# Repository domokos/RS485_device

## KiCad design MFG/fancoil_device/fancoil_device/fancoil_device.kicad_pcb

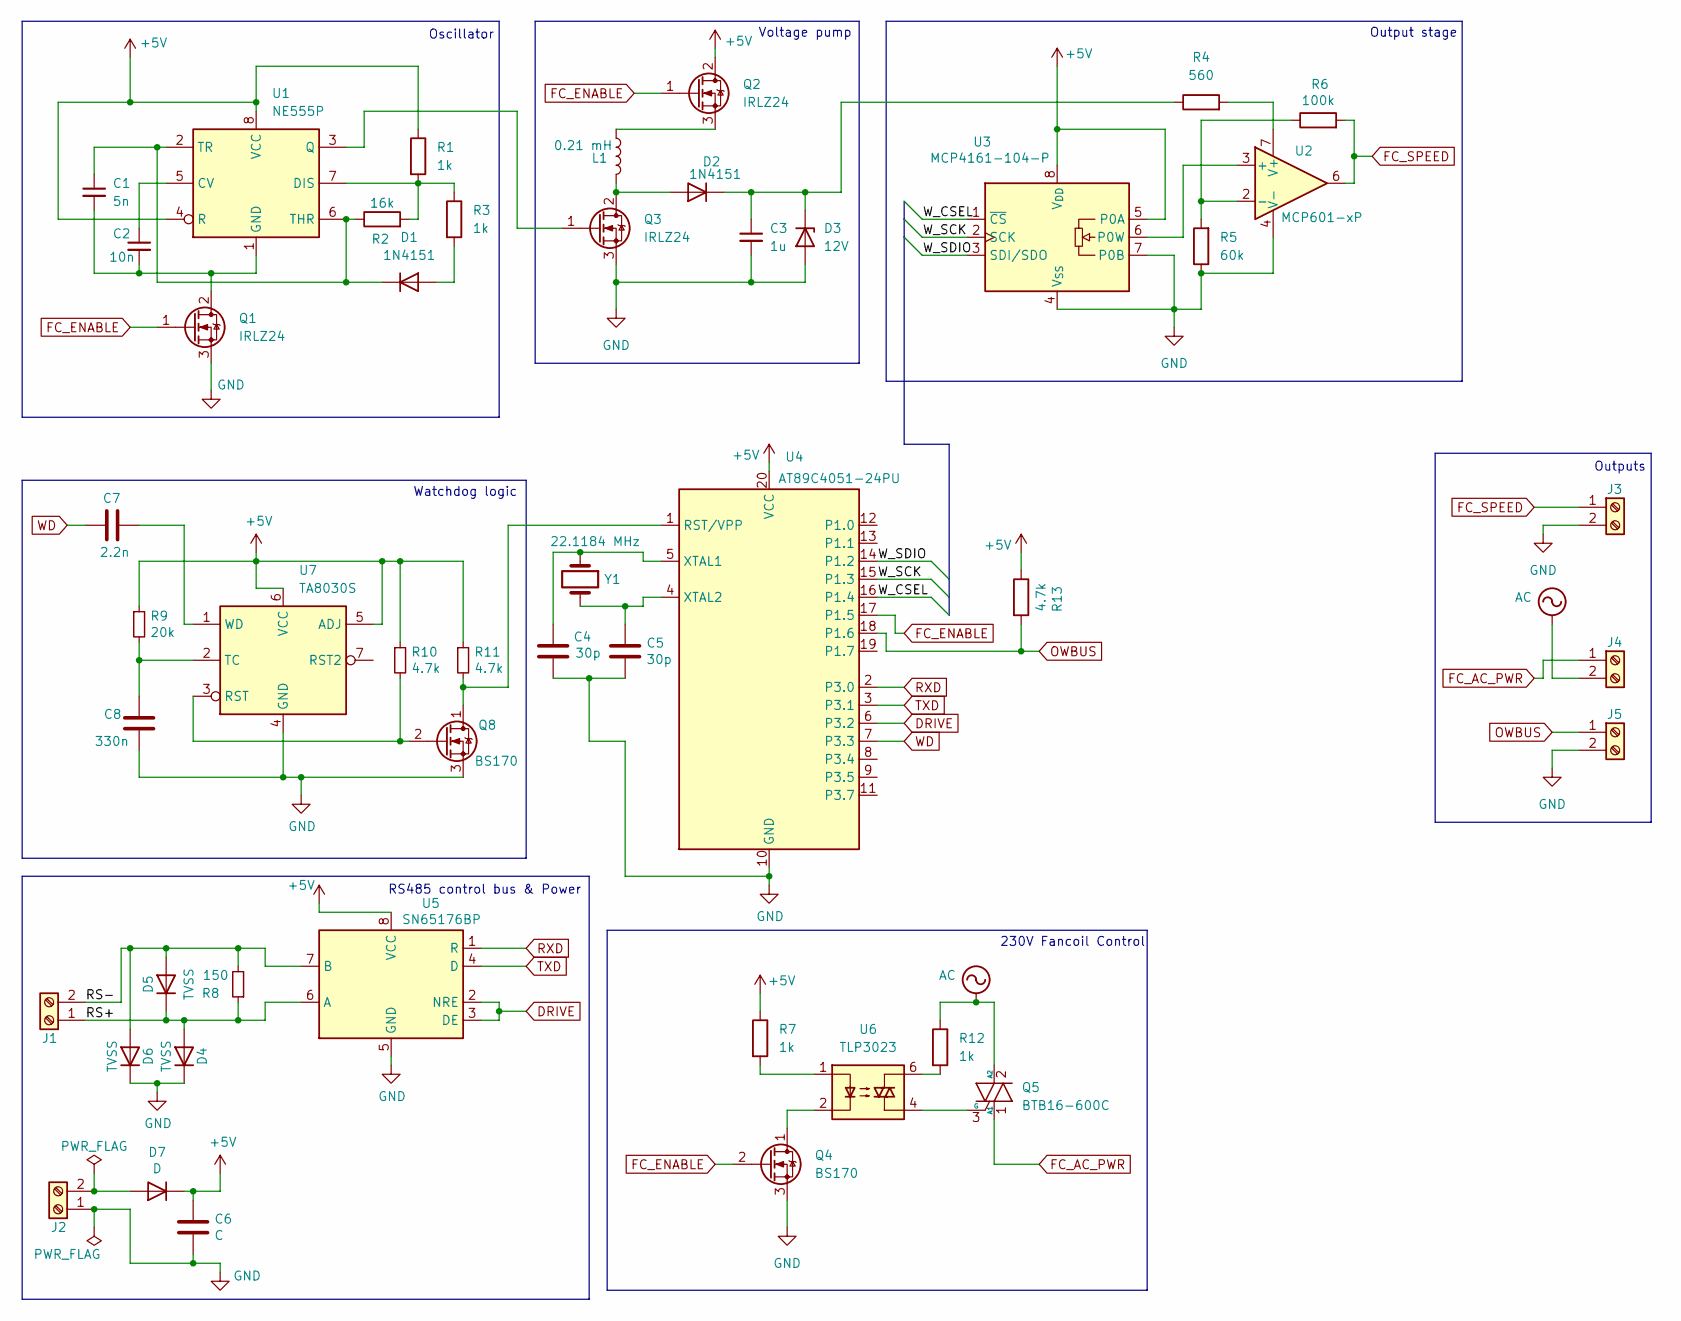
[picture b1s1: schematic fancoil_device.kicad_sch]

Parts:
C1: 5n; C_Disc_D9.0mm_W2.5mm_P5.00mm
C2: 10n; C_Disc_D3.0mm_W2.0mm_P2.50mm
C3: 1u; CP_Radial_Tantal_D4.5mm_P2.50mm
C4, C5: 30p; C_Disc_D3.8mm_W2.6mm_P2.50mm
C6: C; C_Radial_D6.3mm_H11.0mm_P2.50mm
C7: 2.2n; C_Disc_D3.8mm_W2.6mm_P2.50mm
C8: 330n; C_Disc_D3.8mm_W2.6mm_P2.50mm
D1, D2: 1N4151; D_DO-35_SOD27_P7.62mm_Horizontal
D3: 12V; D_A-405_P7.62mm_Horizontal
D4, D5, D6: TVSS; D_5W_P10.16mm_Horizontal
D7: D; D_A-405_P10.16mm_Horizontal
J1, J2, J3, J4, J5: Screw_Terminal_01x02; TerminalBlock_Phoenix_MKDS-1,5-2_1x02_P5.00mm_Horizontal
L1: 0.21 mH; L_Radial_D8.7mm_P5.00mm_Fastron_07HCP
Q1, Q2, Q3: IRLZ24; TO-220-3_Vertical
Q4, Q8: BS170; TO-92_Inline
Q5: BTB16-600C; TO-220-3_Vertical
R1, R3, R7, R12: 1k; R_Axial_DIN0204_L3.6mm_D1.6mm_P5.08mm_Horizontal
R2: 16k; R_Axial_DIN0204_L3.6mm_D1.6mm_P5.08mm_Horizontal
R4: 560; R_Axial_DIN0204_L3.6mm_D1.6mm_P5.08mm_Horizontal
R5: 60k; R_Axial_DIN0207_L6.3mm_D2.5mm_P10.16mm_Horizontal
R6: 100k; R_Axial_DIN0204_L3.6mm_D1.6mm_P5.08mm_Horizontal
R8: 150; R_Axial_DIN0204_L3.6mm_D1.6mm_P5.08mm_Horizontal
R9: 20k; R_Axial_DIN0204_L3.6mm_D1.6mm_P5.08mm_Horizontal
R10, R11, R13: 4.7k; R_Axial_DIN0204_L3.6mm_D1.6mm_P5.08mm_Horizontal
U1: NE555P; DIP-8_W7.62mm
U2: MCP601-xP; DIP-8_W7.62mm
U3: MCP4161-104-P; DIP-8_W7.62mm
U4: AT89C4051-24PU; DIP-20_W7.62mm
U5: SN65176BP; DIP-8_W7.62mm
U6: TLP3023; Toshiba_11-7A9
U7: TA8030S; R_Array_SIP7
Y1: 22.1184 MHz; Crystal_HC49-4H_Vertical

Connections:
+5V: C6.1, D7.1 (K), Q2.2 (D), R1.1, R7.1, R9.1, R10.1, R11.1, R13.1, U1.4 (R), U1.8 (VCC), U3.5 (P0A), U3.8 (V_{DD}), U4.20 (VCC), U5.8 (VCC), U7.5 (ADJ), U7.6 (VCC)
/RS+: D4.2 (A), D5.1 (K), J1.1, R8.1, U5.6 (A)
/RS-: D5.2 (A), D6.2 (A), J1.2, R8.2, U5.7 (B)
/W_CSEL: U3.1 (~CS), U4.16 (P1.4)
/W_SCK: U3.2 (SCK), U4.15 (P1.3)
/W_SDIO: U3.3 (SDI/SDO), U4.14 (P1.2)
AC: J4.2, Q5.2 (A2), R12.1
DRIVE: U4.6 (P3.2), U5.2 (NRE), U5.3 (DE)
FC_AC_PWR: J4.1, Q5.1 (A1)
FC_ENABLE: Q1.1 (G), Q2.1 (G), Q4.2 (G), U4.17 (P1.5)
FC_SPEED: J3.1, R6.2, U2.6
GND: C3.2, C4.2, C5.2, C6.2, C8.2, D3.2 (A), D4.1 (K), D6.1 (K), J2.1, J3.2, J5.2, Q1.3 (S), Q3.3 (S), Q4.3 (S), Q8.3 (S), R5.1, U2.4 (V-), U3.4 (V_{SS}), U3.7 (P0B), U4.10 (GND), U5.5 (GND), U7.4 (GND)
unnamed: D1.2 (A), R3.2
unnamed: C1.1, D1.1 (K), R2.1, U1.2 (TR), U1.6 (THR)
unnamed: D2.2 (A), L1.2, Q3.2 (D)
unnamed: C3.1, D2.1 (K), D3.1 (K), R4.1
unnamed: D7.2 (A), J2.2
unnamed: C1.2, C2.2, Q1.2 (D), U1.1 (GND)
unnamed: L1.1, Q2.3 (S)
unnamed: Q3.1 (G), U1.3 (Q)
unnamed: Q4.1 (D), U6.2
unnamed: Q5.3 (G), U6.4
unnamed: Q8.1 (D), R11.2, U4.1 (RST/VPP)
unnamed: Q8.2 (G), R10.2, U7.3 (RST)
unnamed: R7.2, U6.1
unnamed: R12.2, U6.6
unnamed: C2.1, U1.5 (CV)
unnamed: R1.2, R2.2, R3.1, U1.7 (DIS)
unnamed: U2.3 (+), U3.6 (P0W)
unnamed: R5.2, R6.1, U2.2 (-)
unnamed: R4.2, U2.7 (V+)
unnamed: C4.1, U4.5 (XTAL1), Y1.1
unnamed: C5.1, U4.4 (XTAL2), Y1.2
unnamed: C8.1, R9.2, U7.2 (TC)
unnamed: C7.2, U7.1 (WD)
OWBUS: J5.1, R13.2, U4.18 (P1.6)
RXD: U4.2 (P3.0), U5.1 (R)
TXD: U4.3 (P3.1), U5.4 (D)
WD: C7.1, U4.7 (P3.3)

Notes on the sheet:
Outputs
Oscillator
230V Fancoil Control
Watchdog logic
Output stage
Voltage pump
RS485 control bus & Power

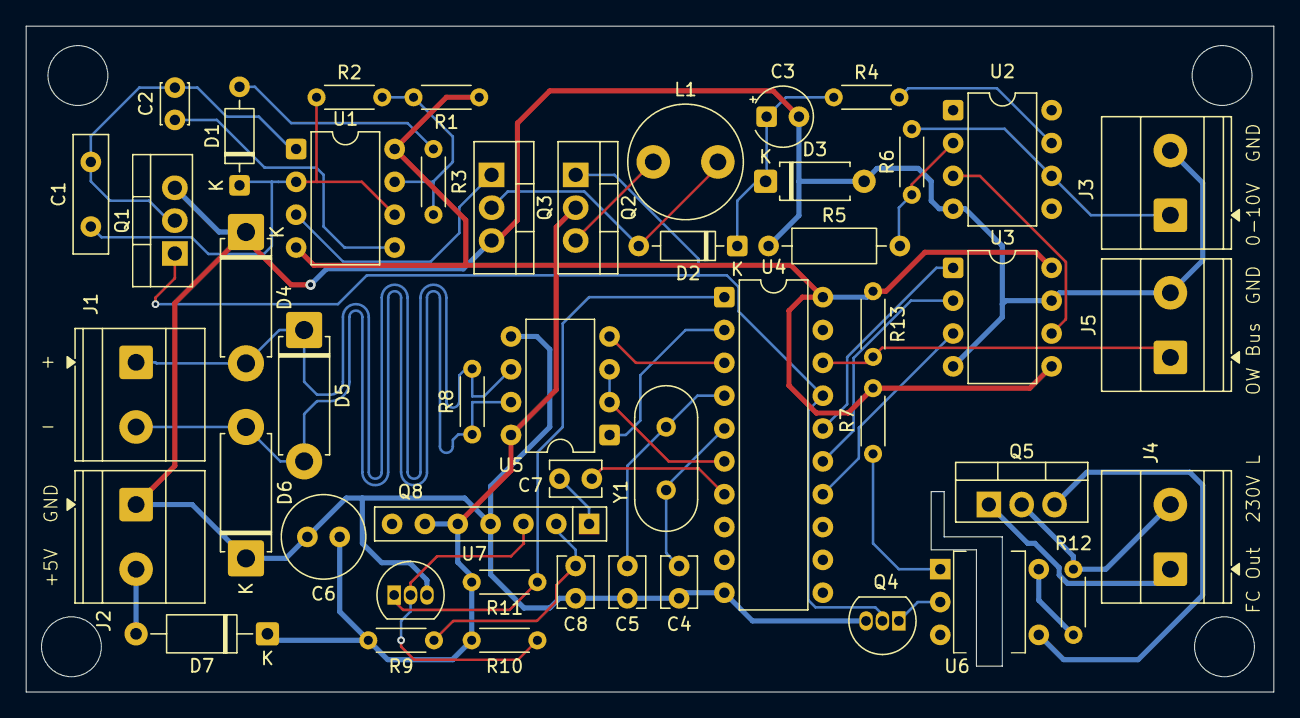
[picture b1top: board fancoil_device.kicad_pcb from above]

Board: 2 copper layers, 96.5 x 51.5 mm, 48 parts (0 on the bottom side), 39 nets.

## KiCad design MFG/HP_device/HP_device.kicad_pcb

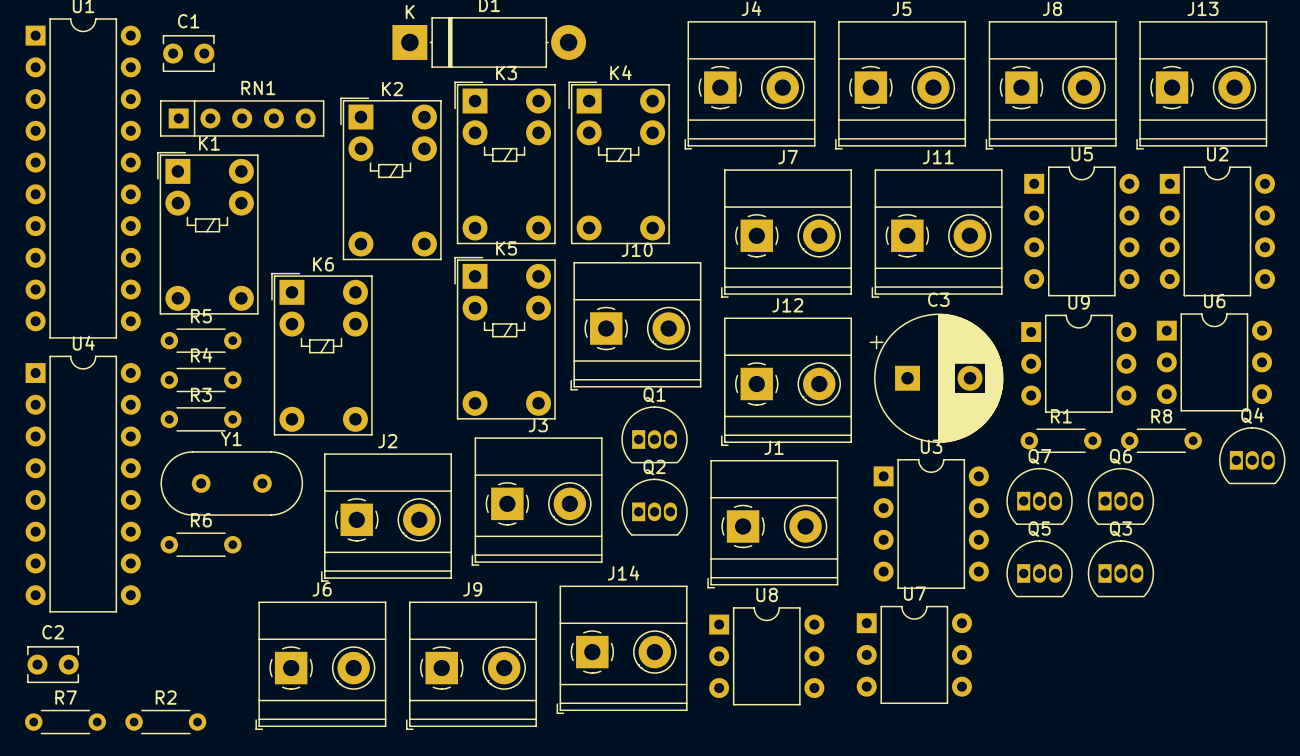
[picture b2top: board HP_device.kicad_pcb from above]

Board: 2 copper layers, 50 parts (0 on the bottom side), 64 nets, no tracks yet.

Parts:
C1, C2: C; C_Disc_D3.8mm_W2.6mm_P2.50mm
C3: C; CP_Radial_D10.0mm_P5.00mm
D1: D; D_5W_P12.70mm_Horizontal
J1, J2, J3, J4, J5, J6, J7, J8, J9, J10, J11, J12, J13, J14: Screw_Terminal_01x02; TerminalBlock_Phoenix_MKDS-1,5-2_1x02_P5.00mm_Horizontal
K1, K2, K3, K4, K5, K6: G5V-1; Relay_SPDT_Omron_G5V-1
Q1, Q2, Q3, Q4, Q5, Q6, Q7: BS170; TO-92_Inline
R1, R6, R7, R8: 4.7k; R_Axial_DIN0204_L3.6mm_D1.6mm_P5.08mm_Horizontal
R2: 200k; R_Axial_DIN0204_L3.6mm_D1.6mm_P5.08mm_Horizontal
R3, R4, R5: R_Small; R_Axial_DIN0204_L3.6mm_D1.6mm_P5.08mm_Horizontal
RN1: 4.7k; R_Array_SIP5
U1: AT89C4051-24PU; DIP-20_W7.62mm
U2: MCP4162-104; DIP-8_W7.62mm
U3: MCP4162-503; DIP-8_W7.62mm
U4: 74HC595; DIP-16_W7.62mm
U5: SN65176BP; DIP-8_W7.62mm
U6, U7, U8, U9: 4N25; DIP-6_W7.62mm
Y1: Crystal; Crystal_HC18-U_Vertical

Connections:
+5V: C3.1, D1.1, K1.2, K2.2, K3.2, K4.2, K5.2, K6.2, R1.1, R6.1, R7.1, R8.2, RN1.1, U1.20, U2.8, U3.8, U4.16, U5.8
/ALARM: RN1.5, U1.11, U9.5
/BCKUP: RN1.4, U1.9, U8.5
/C_DHW: K1.9, Q2.1
/C_DSET: K3.9, Q4.1
/C_LT: K6.9, Q7.1
/C_NOC: K5.9, Q6.1
/C_ON: K2.9, Q3.1
/C_OPM: K4.9, Q5.1
/DHW: Q2.2, U4.1
/DHWA: J9.1, K1.10
/DHWB: J9.2, K1.5, K1.6
/DSET: Q4.2, U4.3
/DSETA: J11.1, K3.10
/DSETB: J11.2, K3.5, K3.6
/EHS: RN1.2, U1.7, U6.5
/LT: Q7.2, U4.6
/LTA: J14.1, K6.10
/LTB: J14.2, K6.5, K6.6
/MODE: RN1.3, U1.8, U7.5
/NMR: U1.17, U4.10
/NOC: Q6.2, U4.5
/NOCA: J13.1, K5.10
/NOCB: J13.2, K5.5, K5.6
/NOE: U1.19, U4.13
/ON: Q3.2, U4.2
/ONA: J10.1, K2.10
/ONB: J10.2, K2.5, K2.6
/OPM: Q5.2, U4.4
/OPMA: J12.1, K4.10
/OPMB: J12.2, K4.5, K4.6
/SERDATA: R6.2, U1.12, U2.3, U3.3, U4.14
/SHCP: U1.16, U4.11
/STCP: U1.18, U4.12
/W_CSEL: Q1.2, R7.2, U1.13, U3.1
/W_SCK: U1.14, U2.2, U3.2
/W_SDO: U1.15, U2.7, U3.7
DRIVE: U1.6, U5.2, U5.3
GND: C1.2, C2.2, C3.2, J2.1, Q1.3, Q2.3, Q3.3, Q4.3, Q5.3, Q6.3, Q7.3, U1.10, U2.4, U3.4, U4.8, U5.5, U6.4, U7.4, U8.4, U9.4
unnamed: C1.1, U1.5, Y1.1
unnamed: C2.1, U1.4, Y1.2
unnamed: D1.2, J2.2
unnamed: J1.1, U5.6
unnamed: J1.2, U5.7
unnamed: J3.1, U6.2
unnamed: J3.2, R2.2
unnamed: J4.1, U7.2
unnamed: J4.2, R3.2
unnamed: J5.1, U8.2
unnamed: J5.2, R4.2
unnamed: J6.1, U9.2
unnamed: J6.2, R5.2
unnamed: J7.1, U2.5
unnamed: J7.2, U2.6
unnamed: J8.1, U3.5
unnamed: J8.2, U3.6
unnamed: Q1.1, R1.2, U2.1
unnamed: R2.1, U6.1
unnamed: R3.1, U7.1
unnamed: R4.1, U8.1
unnamed: R5.1, U9.1
unnamed: R8.1, U1.1
RXD: U1.2, U5.1
TXD: U1.3, U5.4

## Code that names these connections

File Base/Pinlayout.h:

/*
 * Pinlayout.h
 *
 *  Created on: Nov 25, 2014
 *      Author: dmolnar
 */

#ifndef PINLAYOUT_H_
#define PINLAYOUT_H_

/*
 *  This section defines the pins assignments of the microcontroller
 */
#ifdef __CDT_PARSER__

  #define MASTER_HOST_ID
  #define HOST_ID

  #define WATCHDOG_PIN
  #define COMM_DIRECTION_PIN
  // Define on which port the onewire interface is
  #define ONEWIRE_IS_ON_P1

#elif defined MASTER_CONTROLLER_DEVICE
  // Define the ID of this master
  #define MASTER_HOST_ID 1

  #define WATCHDOG_PIN P3_5
  #define COMM_DIRECTION_PIN P1_0

#elif defined MAIN_PANEL_SLAVE_DEVICE
  // The id of this host on the bus
  #define HOST_ID 11

  #define WATCHDOG_PIN P3_3
  #define COMM_DIRECTION_PIN P1_7
  // Define on which port the onewire interface is
  #define ONEWIRE_IS_ON_P3
  #define HEATER_RELAY_PIN P3_5 // Heater contact

#elif defined SIX_OWBUS_SLAVE_DEVICE
  // The id of this host on the bus
  #define HOST_ID 10

  #define WATCHDOG_PIN P3_5
  #define COMM_DIRECTION_PIN P3_7
  // Define on which port the onewire interface is
  #define ONEWIRE_IS_ON_P1

#elif defined MIXER_CONTROL_SLAVE_DEVICE
  // The id of this host on the bus
  #define HOST_ID 12

  #define WATCHDOG_PIN P3_3
  #define COMM_DIRECTION_PIN P1_7
  // Define on which port the onewire interface is
  #define ONEWIRE_IS_ON_P1

#elif defined HP_SLAVE_DEVICE
  // The id of this host on the bus
  #define HOST_ID 13

  #define COMM_DIRECTION_PIN P3_2
  #define EHS_PIN P3_7
  #define MODE_PIN P3_5
  #define BACKUP_PIN P3_4
  #define ALARM_PIN P3_3

#elif defined FANCOIL_SLAVE_DEVICE

  // The id of this host on the bus
  #define HOST_ID 14

  #define WATCHDOG_PIN P3_3
  #define COMM_DIRECTION_PIN P3_2
  // Define on which port the onewire interface is
  #define ONEWIRE_IS_ON_P1

#else
  #error "Basic pinlayout definitions could be determined"
#endif

#ifdef __CDT_PARSER__
  // Define the pins of the SPI interface of the MCP4161
  #define PIN_NCS_HW
  #define PIN_NCS_HEAT
  #define PIN_SCK
  #define PIN_SDI_SDO

  // Main panel heater pin
  #define HEATER_RELAY_PIN

  // Define the pins of the Extender interface of the MCP4161
  #define DS_PIN
  #define NOE_PIN
  #define STCP_PIN
  #define SHCP_PIN
  #define NMR_PIN

  // Define pins of the mixer controller
  #define CCW_PIN
  #define CW_PIN
  #define HW_HP_ONLY_PIN
  #define USEBUFFER_PIN
  #define GPIO_PIN

  // Define pins of the HP device
  #define EHS_PIN
  #define MODE_PIN
  #define BACKUP_PIN
  #define ALARM_PIN
  #define PIN_SERDATA
  #define PIN_SDO
  #define PIN_NCS_CSEL

  // Define pinns of the fancoil device
  #define PIN_FC_ACTIVE

#elif defined MAIN_PANEL_SLAVE_DEVICE
  // Define the pins of the SPI interface of the MCP4161
  #define PIN_NCS_HW P1_0
  #define PIN_NCS_HEAT P1_1
  #define PIN_SCK P3_7
  #define PIN_SDI_SDO P3_4

  // Heater contact
  #define HEATER_RELAY_PIN P3_5

  // Define the pins of the Extender interface
  #define DS_PIN P1_2
  #define NOE_PIN P1_3
  #define STCP_PIN P1_4
  #define SHCP_PIN P1_5
  #define NMR_PIN P1_6

#elif defined HP_SLAVE_DEVICE

  #define PIN_SERDATA P1_3

  // Define the pins of the SPI interface of the MCP4162
  #define PIN_NCS_CSEL P1_0
  #define PIN_SCK P1_1
  #define PIN_SDO P1_2

  // Define the pins of the Extender interface
  #define NOE_PIN P1_4
  #define STCP_PIN P1_5
  #define SHCP_PIN P1_6
  #define NMR_PIN P1_7

#elif defined SIX_OWBUS_SLAVE_DEVICE

#elif defined MASTER_CONTROLLER_DEVICE

#elif defined MIXER_CONTROL_SLAVE_DEVICE

  // Define pins of the mixer controller
  #define CCW_PIN P1_5
  #define CW_PIN P1_6
  #define HW_HP_ONLY_PIN P1_3
  #define USEBUFFER_PIN P1_4
  #define GPIO_PIN P3_7

#elif defined FANCOIL_SLAVE_DEVICE

  // Define the pins of the SPI interface of the MCP4161
  // In this case there is only one potentionmeter wiper in use so we define both chip selector pins to be the
  // same.
  #define PIN_NCS_HW P1_4
  #define PIN_NCS_HEAT P1_4
  #define PIN_SCK P1_3
  #define PIN_SDI_SDO P1_2
  #define PIN_FC_ACTIVE P1_5

#else
  #error "Device specific pinlayout definitions cannot be determined"
#endif

#endif /* PINLAYOUT_H_ */

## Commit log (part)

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2012-10-22 Sync laptop
2012-10-22 Adding functions.
2012-10-26 Fix memory options for build
2012-10-28 Slplit basic functions into a Base.c
2012-10-28 Rename serial to UART
2012-10-28 Add functions to Comm.c
2012-10-29 Start adding message processing logic
2012-10-29 Removing eclipse settings from the project.
2012-10-29 Fix ignoring build componenst on desktop.
2012-10-29 Fix encoding to ISO-8859-2.
2012-10-30 Finalize message reception logic
2012-10-30 Complete communication routines.
2012-10-30 Correct typo of buffer clearing.
2012-10-31 Get rid of the top level subdirectory structure.
2012-10-31 Fix: Put ISR prototypes in the same file that contains main().
2012-11-01 Fix interrupt enable and send buffer numbering.
2012-11-01 Fix messaging logic sync based on emulator tests.
2012-11-01 Add simple test. This commit works in the emulator.
2012-11-02 CRC16 working. / cleanup to use it.
2012-11-04 Implement flip_bit - not yet tested
2012-11-06 Bring bit flipping into the crc calculation. Not yet tested in emulator.
2012-11-06 Clean up Comm.h
2012-11-06 16 bit CSR calculation works with flippped bits in ermulator.
2012-11-10 CRC calculation works and tested in the emulator. TODO: Test response CRC
2012-11-10 CRC tested in-out in emulator. TODO:write tests for HW bus comm and test it :)
2013-01-29 Create own header file for at89c4051 registers to handle eclipse errors.
2013-02-01 Add interface functions to comm module
2013-02-01 Define message opcodes
2013-02-02 Reorganize functions
2013-02-04 Implement tests for hardware test.
2013-02-07 Fix documetation typos and cleanup prev_recieved char in Comm.c
2013-02-10 Add communication transciever handling
2013-02-11 Add flood test to the comm module.
2013-02-11 Fix some typo in comments and in CRC_ERROR #define
2013-02-11 Verify delay routines
2013-02-11 Moving to laptop
2013-02-12 Cleanup timeout calculation in receive message.
2013-02-12 SOme optimizations around receive state machine
2013-02-12 Fix test sequences
2013-02-13 Add testing facilities.
2013-02-15 Modifying test code
2013-02-16 Cleanup and implement circular buffer based UART communication
2013-02-16 Communication mode changed to length based and tested succesfully in the emulator.
2013-02-18 Reorganize into devices and master controller step1
2013-02-18 Reorganization almost done
2013-02-18 Finallize reorganization. Succesfully tested in emulator.
2013-02-19 Reorganize to implement Master controller.
2013-02-19 Reorganize: move common functionality into Comm_common module.
2013-02-19 Add master address and start implementing master conrtoller.
2013-02-19 Fix compile issues.
2013-02-19 Start implementing timer1 clock based messaging timeout counter for reliability and for bus master messaging timeout measurements.
2013-02-19 Change HI-LO timeout information to bit
2013-02-20 Add timeout handling routines
2013-02-20 Update calculations
2013-02-21 Reorganized delay and timeout to correct time base and test it in emulator.
2013-02-22 Bus master done todo: test it in emulator
2013-02-23 Workaround SDCC bug. Tested on protoboard. Works.
2013-02-24 COmments cleanup.
2013-02-24 Handle MSG_TOO_LONG in receiving
2013-02-25 Resove referencing NULL pointer as message buffer.
2013-02-26 Reorganize master communication and add new message types.
2013-02-27 Reorganize return values of get_messge
2013-02-27 Add onewire lib
2013-02-27 Continued onewire integration.
2013-02-28 MOdify onewire to accept pinmask and start onewire test implementation.
2013-02-28 Onewire tested in emulator
2013-03-01 Start temp measuring device and reorganize comm_speed based on two crystal speeds.
2013-03-01 Reorganized for generic device.
2013-03-01 Start ow temp measuring implementation
2013-03-01 Temp measure and read tone. Test it in emulator then with HW.
2013-03-02 Start temp reader device testing in emulator.
2013-03-02 1wire Measured with scope. Seems OK.
2013-03-03 Communicates temperature correctly on protoboard.
2013-03-04 add temp measurement timeout
2013-03-04 Investigating timeout. Not yet found.
    Device sometimes does not respond to messages getting to UART pin for
    unknown reason.
2013-03-05 Testing comm problems
2013-03-05 Clean testing code from master.
2013-03-05 Cleanup before branch
2013-03-05 Tested with scope & protoboard. Works.
2013-03-06 COmm error rate down to 4%. Hmmmm.
2013-03-06 Still errors a bit.
2013-03-06 Refine get_message
2013-03-06 Fixed timeout errors. Timeout error rate below 0.1%
2013-03-06 Distribute onewire reads in time.
2013-03-11 Add watchdog functionality.
2013-03-12 Refine timer in Base and equalize interrupt priorities
2013-03-12 Change watchdog pin.
2013-03-12 Add schematics
2013-03-12 Add symbols
2013-03-13 Start drawing schematic.
2013-03-14 Finish schematic.
2013-03-15 Add symbols, finalize schematic.
2013-03-15 Schematics refining
2013-03-15 Finalize resistor values.
2013-03-16 Change crystal frequency and make init timer pulic.
2013-03-16 Reorganize schematics and pcbs
2013-03-17 Work on pcb
2013-03-17 Refine serial tx.
2013-03-17 fix packaging of optocoupler.
2013-03-18 Refine pcb once more.
2013-03-18 Cleanup generated files.
2013-03-18 Add onewire 3 device
2013-03-18 Reorganize symbols.
2013-03-20 Rename things
2013-03-21 Finalize elements in ow6 layout
2013-03-21 Finish PCB
2013-03-21 fixups on layout.
2013-03-22 Prited PCBs.
2013-03-23 Add alignment marks to PCB layout
2013-03-25 Test the panel. MOdify watchdog resistor and ADJ values.
2013-03-29 Finalize master controller
2013-03-30 Add structure for main panel device based on generid test device.
2013-03-30 Reorganize further.
2013-03-31 Add registers.
2013-03-31 Write registers
2013-03-31 Master panel ready for HW testing.
2013-04-01 PWM is complete. Need to add PWM mesage handling before testing.
2013-04-02 Clarify comments.
2013-04-02 Implemented multiple OW devices on a single bus. Needs testing.
2013-04-02 PWM and single OW tested in hardware. Works. To be tested mutiple OW on a bus.
2013-04-03 Reorganize PWM
2013-04-03 OPtimize PWM state machine.
2013-04-03 Tested in device. Works.
2013-04-08 ROM ID read succesfully with test device.
2013-04-09 Multiple OW devices on single bus works, tested in Main Panel Device.
2013-04-11 Reorganize panels and add comm safety to Master controller.
2013-04-11 fix small typo.
2013-04-13 Prepare branching comm for interrupt driven serial receiving.
2013-04-13 Fix eclipse parser mocking.
2013-04-13 Messaging restructured. Ready for testing.
2013-04-16 REN based strategy in ISR receiving. Needs testing.
2013-04-16 Some ISR-receiver hadshaking and timeout fixes before testing.
2013-08-04 Modify layout of 6owbus - join powe & GND lines to a single connector.
2013-08-23 Add 6 ow bus device.
2013-08-25 OW interface of 6 OW bus device tested.
2013-08-28 Add alternative Master controller PCB
2013-08-31 Modify master controller layout
2013-08-31 Fine tune master controller pcb
2013-09-01 Finalize Master controller PCB layout
2013-09-03 Fine tune layout and add printed ps file
2013-09-16 Fix optocoupler in master_controller MFG
2013-10-01 New version of master_controller MFG
2013-12-28 Continue Design of main panel device
2014-01-19 Main controller PCB design started
2014-01-19 Further elaborate main controller MFG.
2014-01-23 Fix missing resistor and add 230V signal components
2014-01-25 Create 230V parts of board
2014-01-26 Finish first version of PCB fine tune layout connections.
2014-02-08 Fix wirting of optocoupler inputs.
2014-03-03 Change 230V capacitor to a bigger one.
2014-03-16 Add a different size line capacitor.
2014-03-17 Fine tune layout
2014-05-02 Add text and alignment mark to main panel PCB
2014-11-13 Modify main panel device for new condensing boiler.
2014-11-17 Revert a file
2014-11-18 Finalize board before printing
2014-11-23 Finalize layout. Correct Triac pinout and schematic.
2014-11-23 Fix relay pcb in main panel board
2014-11-23 Add MCP4161 code
2014-11-25 Reorganize pinlayout definitions.
2014-11-25 Fixed missing component from main panel device
2014-11-26 Fixes of the main panel device after first debugging session.
2014-11-26 Fix wiper setting.
2014-11-27 Fix spi timing for MCP4161
2014-11-27 Finalize and test rheostat timing
2014-11-30 Onewire device addresses set for final operation.
2014-11-30 Update contact comments in the controller code
2014-12-01 Fix HW problems and test.
2014-12-01 Fix typo in scaling
2014-12-07 Fix command bytes
2014-12-07 Re-fix wiper write volatility
2014-12-07 Fix reading wiper volatility flag
2014-12-14 Branch for time-distributed sensor read on the single bus
2014-12-15 Rework main panel schematic
2014-12-16 Finalize schematics - add 2 new switches and a rheostat
2014-12-16 Add original rheostat drawing
2014-12-17 Start working on pcb layout
2014-12-18 Develop layout further
    Please enter the commit message for your changes. Lines starting
2014-12-18 Finish Layout
2014-12-18 Reduce vias in the pcb
2014-12-19 Remove some vias
2014-12-24 Add mounting holes to pcb
2014-12-25 Reorganize board to make moore room
2014-12-25 Finalize layout
2014-12-26 Create hidraulic schematic
2014-12-26 Add alignment marks to the pcb layout
2014-12-26 Rename file
2014-12-27 Modify hidraulic drawing
2014-12-29 MOve main panel device to single extender code
2014-12-29 Fix extender reset and buffer initialize bugs.
2014-12-29 Swap extender bit order
2014-12-29 Adjust main panel device inactivity self-reset timeout to 30 sec
2014-12-29 Tested in Hardware - cleanup comments and contact assignments in code
2014-12-31 Disable messaging timeout as it did not work.
2014-12-31 Fix pinlayout defines by introducing device specfic compiler defines
2014-12-31 Make all pind device type define dependent
2015-01-01 Fix defines for Exclipes CDT parser
2015-01-03 Fix typo of Exclipse parser name
2015-01-03 Start implementing the owbus bridge
2015-01-03 Start HW testing six owbus device
2015-01-03 Prepare for in-HW testing
2015-01-03 Fix messaging
2015-01-03 Fix direction pin
2015-01-03 Swap search byte order
2015-01-03 Test owbuf in match active
2015-01-03 Fix typos in debug code
2015-01-03 Lab test preparation
2015-01-03 Restore real device addresses
2015-01-04 Fix ow temp measurement initiation
2015-01-04 Fix addressing of registers
2015-01-30 Create new device - compiles
2015-02-03 Add layout elements for mixer controller
2015-02-04 Finish schematic - create initial PCB
2015-02-06 Finalize layout of mixer controller
2015-02-11 Prepare mixer logic
2015-02-14 Finalize mixer controller
2015-02-14 Reorganize pinlayour defines
2015-02-22 Add ROM code for address for forward floor temp.
2015-05-31 Add empty eventcounter files to project
2015-05-31 Add event counter module
2015-11-22 Set addresses of forwar and return temp sensors
2015-12-29 Fix single extender register read
2016-01-03 Change address of upstairs sensor
2018-01-09 Increase timeout for messaging.
2018-12-28 Lower value of optocoupler trigger current resistor to increase current. Add pullup resistor to onewrire bus Suppress compiler warnings.
2019-10-05 Add an extra sensor to MixerController device
2022-10-16 Rename sensors n comments / no logic change
2022-11-07 Add HP device schematic
2022-11-07 Further simplify flip logic in mixer controller
2022-11-07 Invert switching logic of Temporary DHW HP contact
2022-11-07 Fix Temporary HW temp relay initial position
2022-11-07 Add layouts
2022-11-07 Fix inverting return value of inverted logic switc on mixer cntroller
2022-11-07 HP device scheamtic complete with footprints
2022-11-07 Fix another typo in mixer controller invert logic
2022-11-07 Add temporarily onewire contacts for HP to Mixer controller
2022-11-07 Fix schematic
2022-11-07 Tested on bench ready for in comms test over RS486
2022-11-07 leanup after rebase
2022-11-17 Remove temp devices, add comm reset timer
2026-01-04 Fix compiler warning "no prototype"
2026-01-07 Fix improper regiter use and reorganize common MCP416x code
2026-01-07 Fix naming
2026-01-10 Add new files
2026-02-07 Test of Fancoil device OK
